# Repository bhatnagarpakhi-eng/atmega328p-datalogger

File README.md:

# ATmega328P Datalogger PCB

A custom-designed data logging PCB built around the ATmega328P microcontroller, featuring real-time clock functionality and expanded non-volatile storage. Designed in KiCad 9.0 as a hands-on PCB design project, covering schematic capture, layout, routing, and design rule verification across two board variants.

## Overview

This project is a compact datalogger board with:
- **MCU:** ATmega328P
- **RTC:** DS3231 (high-precision real-time clock)
- **Storage:** 512KB EEPROM
- **Connectors:** ICSP header, GPIO breakout, serial header, power connectors
- **Crystal oscillators:** 16MHz (MCU clock) + 32.768kHz (RTC)
- **Indicators:** Onboard LEDs for status feedback

The board was developed in two layout variants — a 2-layer version and a 4-layer version — to explore how additional copper layers affect power/ground plane integrity and routing density.

## Repository Structure

This repo uses a branch-per-layout strategy:

- **`main`** — canonical schematic, project files, and documentation. Does not contain a finalized PCB layout (see branches below for actual board files).
- **`2-layer`** — 2-layer PCB layout and routing.
- **`4-layer`** — 4-layer PCB layout and routing.

Schematic changes are made on `main` and pulled into each layout branch via `Update from main`. PCB layout files are kept separate per branch to avoid merge conflicts between the two distinct board designs.

## Renders

**4-Layer Board:**

**2-Layer Board:**

*(Renders exported from KiCad's 3D Viewer, available on their respective branches.)*

## Design Verification

### Schematic (ERC)
✅ **0 errors, 0 warnings** — verified clean on `main`.

### 4-Layer PCB (DRC)
✅ **0 errors** — fully clean. Dedicated internal power/ground plane layers provided sufficient copper for proper thermal relief connections across all pads.

### 2-Layer PCB (DRC)
⚠️ **4 known errors, 32 warnings (unresolved by design choice)**

- **4 thermal relief / isolated island errors** on GND and VCC zones (affecting J1, J2, R2 pads). Root cause: tight routing clearance between a VCC trace and nearby GND/VCC pads pinched off zone copper pour at those specific points. Attempted fixes (zone re-fill, hatch-to-solid fill type change, minor rerouting) did not fully resolve the geometry constraint.
- **32 warnings** — primarily silkscreen text height falling under the board's configured minimum (0.7mm actual vs 0.8mm constraint) and one silkscreen overlap. Cosmetic only.

**Why these remain unresolved:** This board is not intended for fabrication — it served as the 2-layer baseline for comparison against the 4-layer design. The 4-layer board's clean DRC result directly demonstrates how added plane layers resolve the exact grounding constraint the 2-layer version hit. This is intentionally documented here as a real finding from the design process rather than hidden.

## Tools Used

- KiCad 9.0 (schematic capture, PCB layout, 3D visualization)
- Git / GitHub Desktop (version control)

## Getting Started

To explore a specific board layout:
```bash
git clone https://github.com/bhatnagarpakhi-eng/atmega328p-datalogger.git
cd atmega328p-datalogger
git checkout 4-layer   # or 2-layer
```
Open `mcu datalogger.kicad_pro` in KiCad 9.0 or later.

## Author

Pakhi Bhatnagar
[GitHub](https://github.com/bhatnagarpakhi-eng) · [LinkedIn](https://linkedin.com/in/pakhi-bhatnagar-a49428306)

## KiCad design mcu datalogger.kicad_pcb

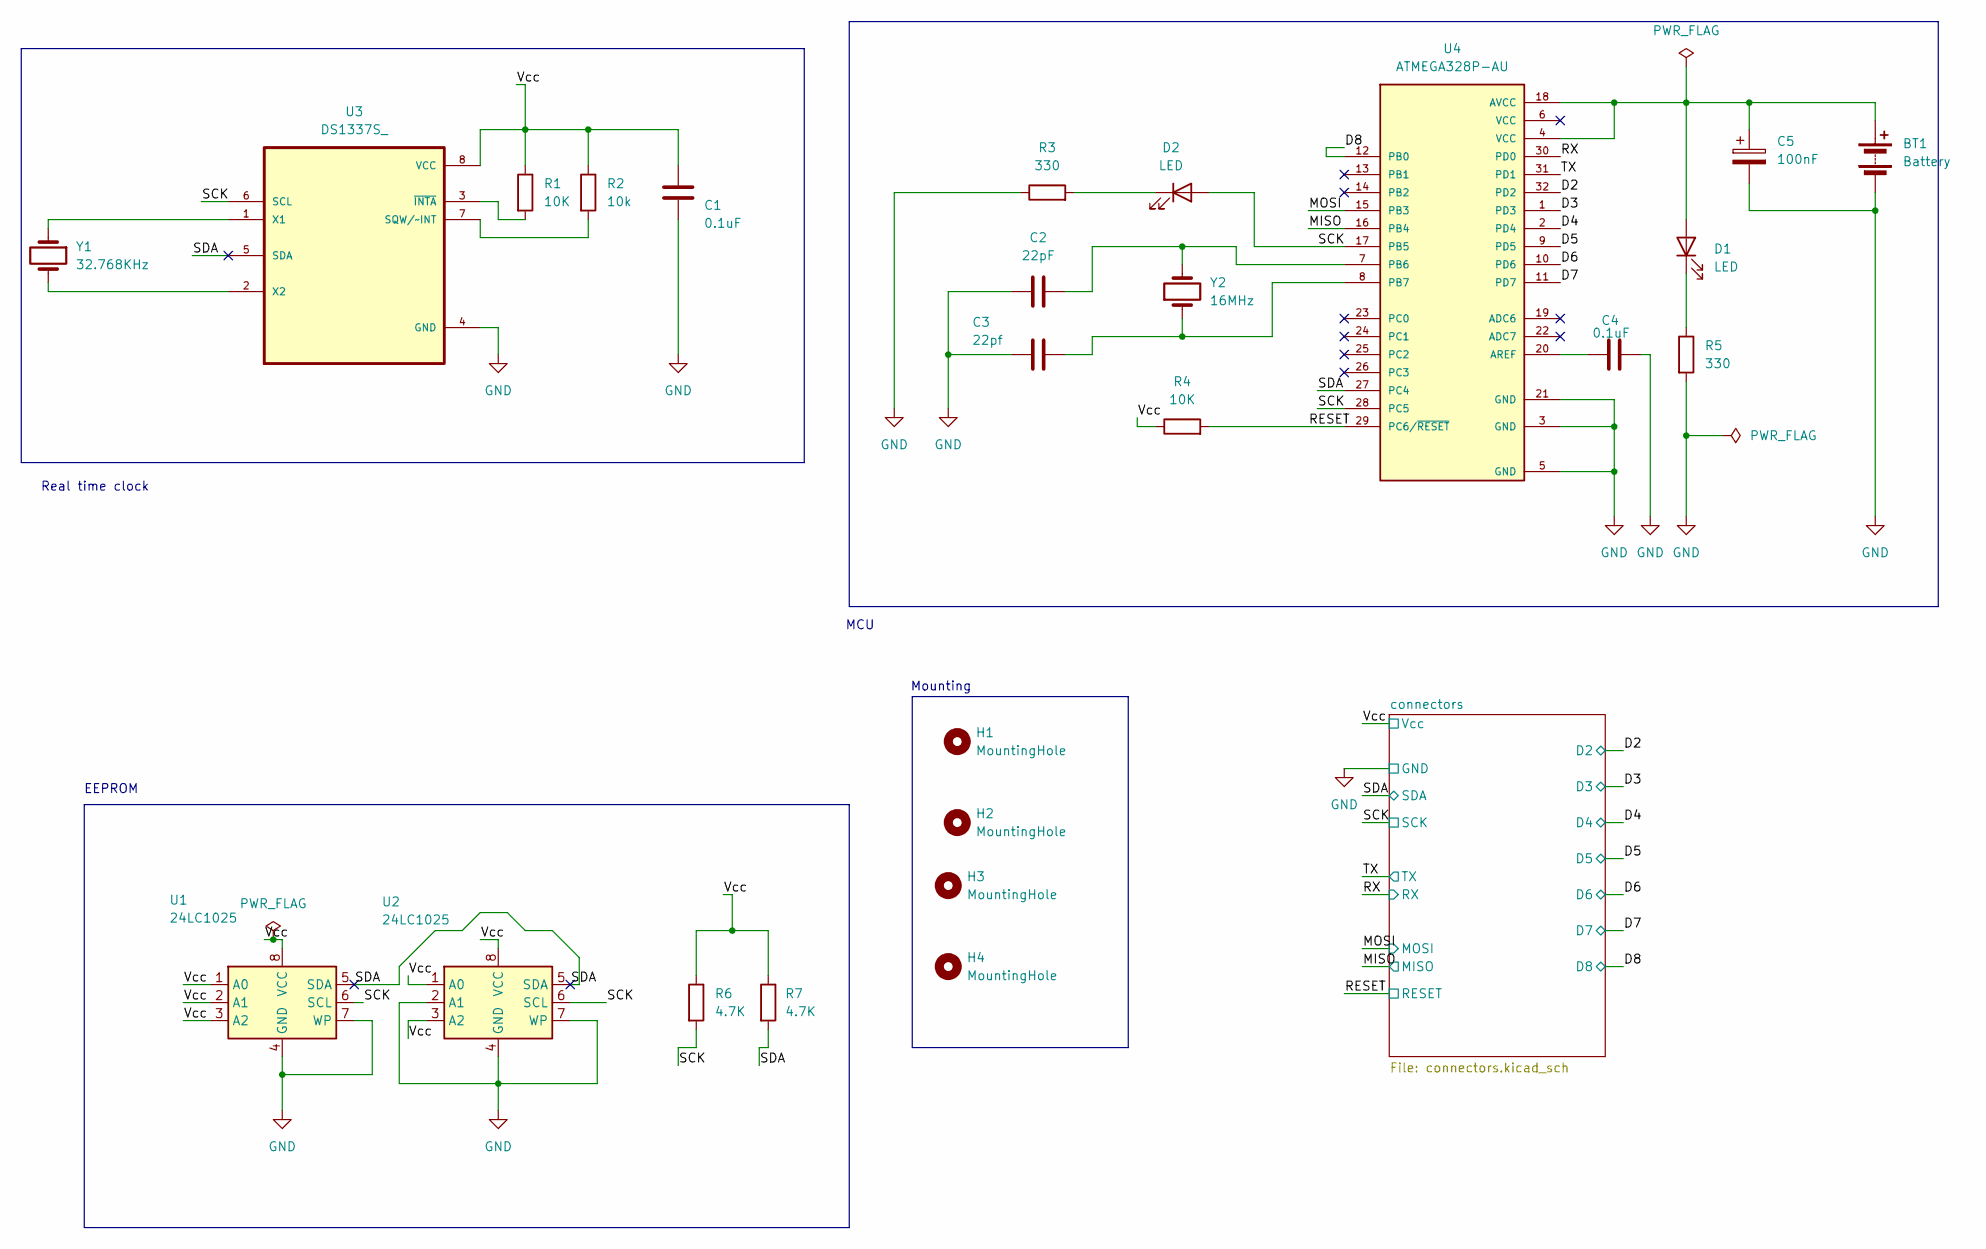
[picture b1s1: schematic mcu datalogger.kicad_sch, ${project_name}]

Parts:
BT1: Battery; PinHeader_1x02_P2.54mm_Vertical
C1, C4: 0.1uF; C_0805_2012Metric
C2: 22pF; C_0805_2012Metric
C3: 22pf; C_0805_2012Metric
C5: 100nF; C_0805_2012Metric
D1, D2: LED; LED_0805_2012Metric
H1, H2, H3, H4: MountingHole; MountingHole_2.1mm
R1, R4: 10K; R_0805_2012Metric
R2: 10k; R_0805_2012Metric
R3, R5: 330; R_0805_2012Metric
R6, R7: 4.7K; R_0805_2012Metric
U1, U2: 24LC1025; SOIC-8_5.3x5.3mm_P1.27mm
U3: DS1337S_; SOIC127P600X175-8N
U4: ATMEGA328P-AU; QFP80P900X900X120-32N (2); PARTREV 8271A
Y1: 32.768KHz; Crystal_SMD_5032-2Pin_5.0x3.2mm_HandSoldering
Y2: 16MHz; Crystal_SMD_5032-2Pin_5.0x3.2mm_HandSoldering

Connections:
/D2: U4.32 (PD2); also elsewhere on the board
/D3: U4.1 (PD3); also elsewhere on the board
/D4: U4.2 (PD4); also elsewhere on the board
/D5: U4.9 (PD5); also elsewhere on the board
/D6: U4.10 (PD6); also elsewhere on the board
/D7: U4.11 (PD7); also elsewhere on the board
/D8: U4.12 (PB0); also elsewhere on the board
/MISO: U4.16 (PB4); also elsewhere on the board
/MOSI: U4.15 (PB3); also elsewhere on the board
/RESET: R4.2, U4.29 (PC6/~RESET); also elsewhere on the board
/RX: U4.30 (PD0); also elsewhere on the board
/SCK: D2.2 (A), R6.2, U1.6 (SCL), U2.6 (SCL), U3.6 (SCL), U4.17 (PB5), U4.28 (PC5); also elsewhere on the board
/SDA: R7.2, U1.5 (SDA), U2.5 (SDA), U3.5 (SDA), U4.27 (PC4); also elsewhere on the board
/TX: U4.31 (PD1); also elsewhere on the board
/Vcc: C1.1, R1.1, R2.1, R4.1, R6.1, R7.1, U1.1 (A0), U1.2 (A1), U1.3 (A2), U1.8 (VCC), U2.1 (A0), U2.3 (A2), U2.8 (VCC), U3.8 (VCC); also elsewhere on the board
GND: BT1.2 (-), C1.2, C2.1, C3.1, C4.2, C5.2, R3.1, R5.2, U1.4 (GND), U1.7 (WP), U2.2 (A1), U2.4 (GND), U2.7 (WP), U3.4 (GND), U4.3 (GND), U4.5 (GND), U4.21 (GND); also elsewhere on the board
unnamed: BT1.1 (+), C5.1, D1.2 (A), U4.4 (VCC), U4.18 (AVCC)
unnamed: D1.1 (K), R5.1
unnamed: D2.1 (K), R3.2
unnamed: R2.2, U3.7 (SQW/~INT)
unnamed: U3.1 (X1), Y1.1
unnamed: U3.2 (X2), Y1.2
unnamed: R1.2, U3.3 (~INTA)
unnamed: C4.1, U4.20 (AREF)
unnamed: C2.2, U4.7 (PB6), Y2.2
unnamed: C3.2, U4.8 (PB7), Y2.1

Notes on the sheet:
Mounting
EEPROM
MCU
Real time clock

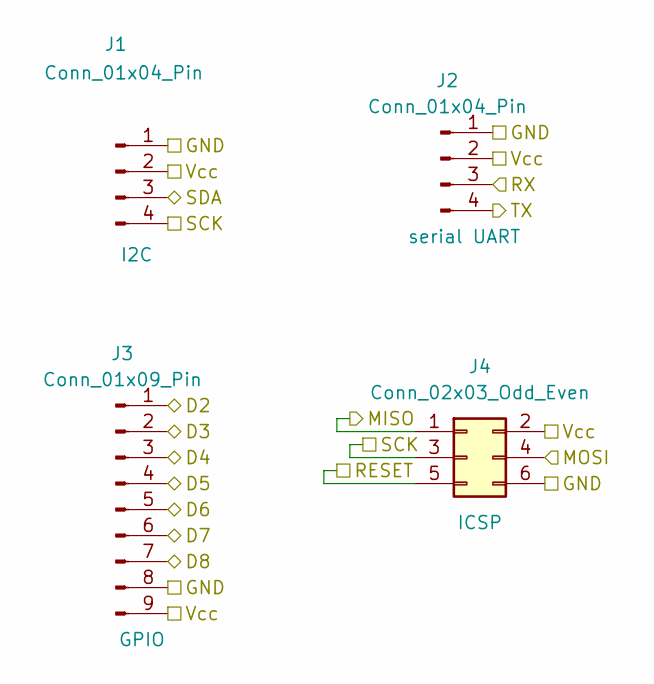
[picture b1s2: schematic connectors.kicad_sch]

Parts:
J1, J2: Conn_01x04_Pin; PinHeader_1x04_P2.54mm_Vertical
J3: Conn_01x09_Pin; PinHeader_1x09_P2.54mm_Vertical
J4: Conn_02x03_Odd_Even; PinHeader_2x03_P2.54mm_Vertical

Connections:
/D2: J3.1; also elsewhere on the board
/D3: J3.2; also elsewhere on the board
/D4: J3.3; also elsewhere on the board
/D5: J3.4; also elsewhere on the board
/D6: J3.5; also elsewhere on the board
/D7: J3.6; also elsewhere on the board
/D8: J3.7; also elsewhere on the board
/MISO: J4.1; also elsewhere on the board
/MOSI: J4.4; also elsewhere on the board
/RESET: J4.5; also elsewhere on the board
/RX: J2.3; also elsewhere on the board
/SCK: J1.4, J4.3; also elsewhere on the board
/SDA: J1.3; also elsewhere on the board
/TX: J2.4; also elsewhere on the board
/Vcc: J1.2, J2.2, J3.9, J4.2; also elsewhere on the board
GND: J1.1, J2.1, J3.8, J4.6; also elsewhere on the board

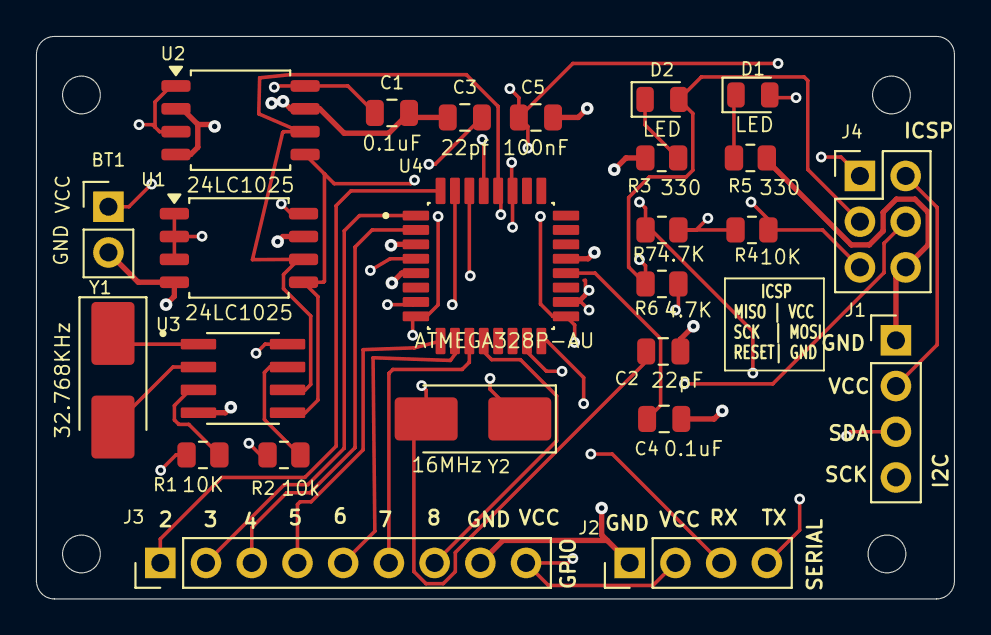
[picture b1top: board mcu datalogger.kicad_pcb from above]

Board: 4 copper layers, 51.0 x 31.2 mm, 29 parts (0 on the bottom side), 26 nets.

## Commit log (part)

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2026-06-08 Add initial KiCad schematic with components placed
2026-06-10 Completed symbols to footprints associations
2026-06-11 Completed wiring of main sheet
2026-06-12 Completed wiring and ERC check for root sheet
2026-06-12 Completed wirings for connector sheet
2026-06-15 Completed comments
2026-06-15 Setup pcbnew
2026-06-15 Completed placement of footprints
2026-06-18 Routing sans GND and Vcc completed
2026-06-18 Completed routing
2026-06-19 Fixed outstanding issues
2026-06-19 Completed 2 layer PCB project
2026-06-20 Completed 4 layer pcb routing
2026-06-20 Add schematic annotations and documentation to 4-layer design
2026-06-20 Configure KiCad files for union merge strategy
